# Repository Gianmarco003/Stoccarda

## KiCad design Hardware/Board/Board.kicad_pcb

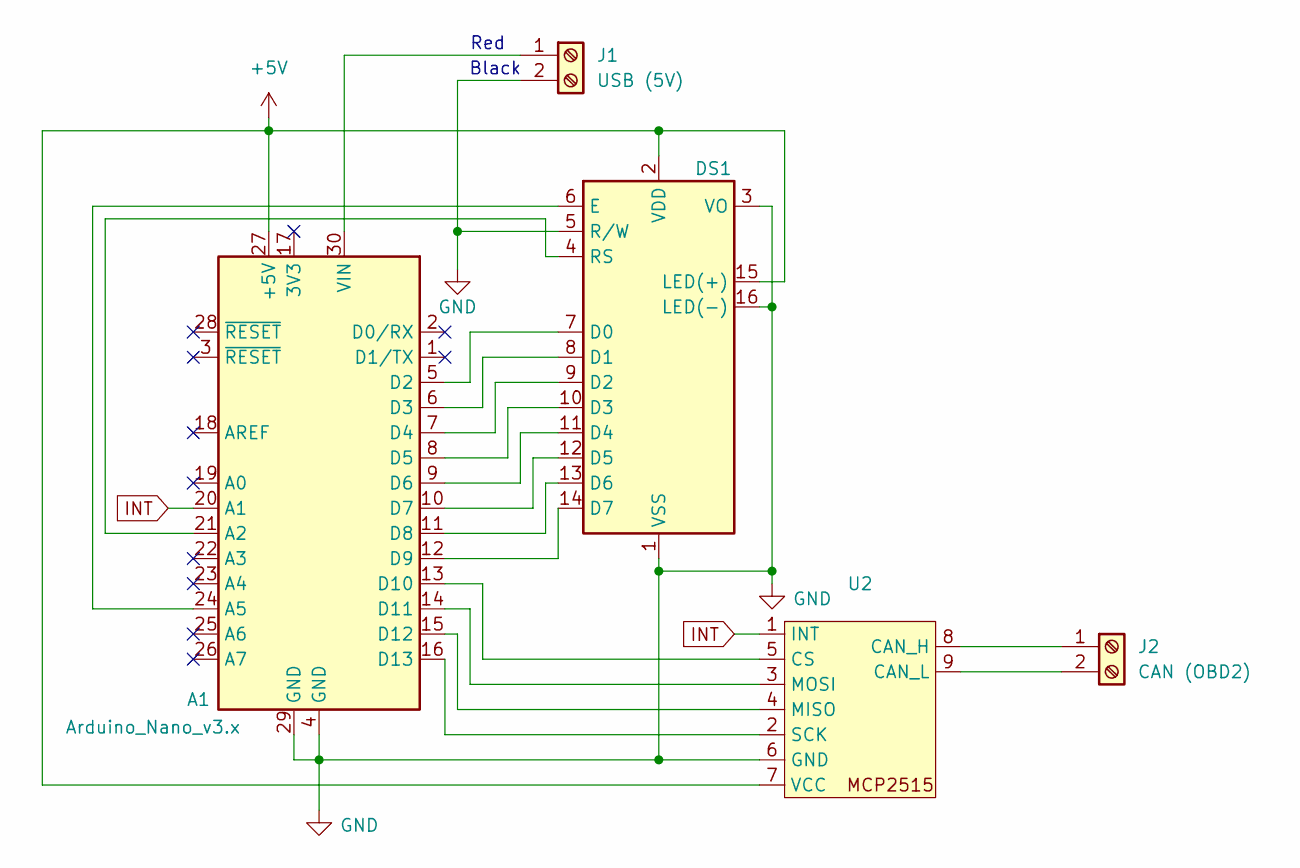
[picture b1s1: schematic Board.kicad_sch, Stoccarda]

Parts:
A1: Arduino_Nano_v3.x; Arduino_Nano
DS1: WC1602A; Display 20x4
J1: USB (5V); PhoenixContact_GMSTBVA_2,5_2-G-7,62_1x02_P7.62mm_Vertical
J2: CAN (OBD2); PhoenixContact_GMSTBVA_2,5_2-G-7,62_1x02_P7.62mm_Vertical
U2: MCP2515 board

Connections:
+5V: A1.27 (+5V), DS1.2 (VDD), DS1.15 (LED(+)), U2.7 (VCC)
GND: A1.4 (GND), A1.29 (GND), DS1.1 (VSS), DS1.3 (VO), DS1.5 (R/W), DS1.16 (LED(-)), J1.2, U2.6 (GND)
INT: A1.20 (A1), U2.1 (INT)
unnamed: A1.21 (A2), DS1.4 (RS)
unnamed: A1.24 (A5), DS1.6 (E)
unnamed: A1.5 (D2), DS1.7 (D0)
unnamed: A1.6 (D3), DS1.8 (D1)
unnamed: A1.7 (D4), DS1.9 (D2)
unnamed: A1.8 (D5), DS1.10 (D3)
unnamed: A1.9 (D6), DS1.11 (D4)
unnamed: A1.10 (D7), DS1.12 (D5)
unnamed: A1.11 (D8), DS1.13 (D6)
unnamed: A1.12 (D9), DS1.14 (D7)
unnamed: A1.13 (D10), U2.5 (CS)
unnamed: A1.14 (D11), U2.3 (MOSI)
unnamed: A1.15 (D12), U2.4 (MISO)
unnamed: A1.16 (D13), U2.2 (SCK)
unnamed: A1.30 (VIN), J1.1
unnamed: J2.1, U2.8 (CAN_H)
unnamed: J2.2, U2.9 (CAN_L)

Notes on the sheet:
Black
Red

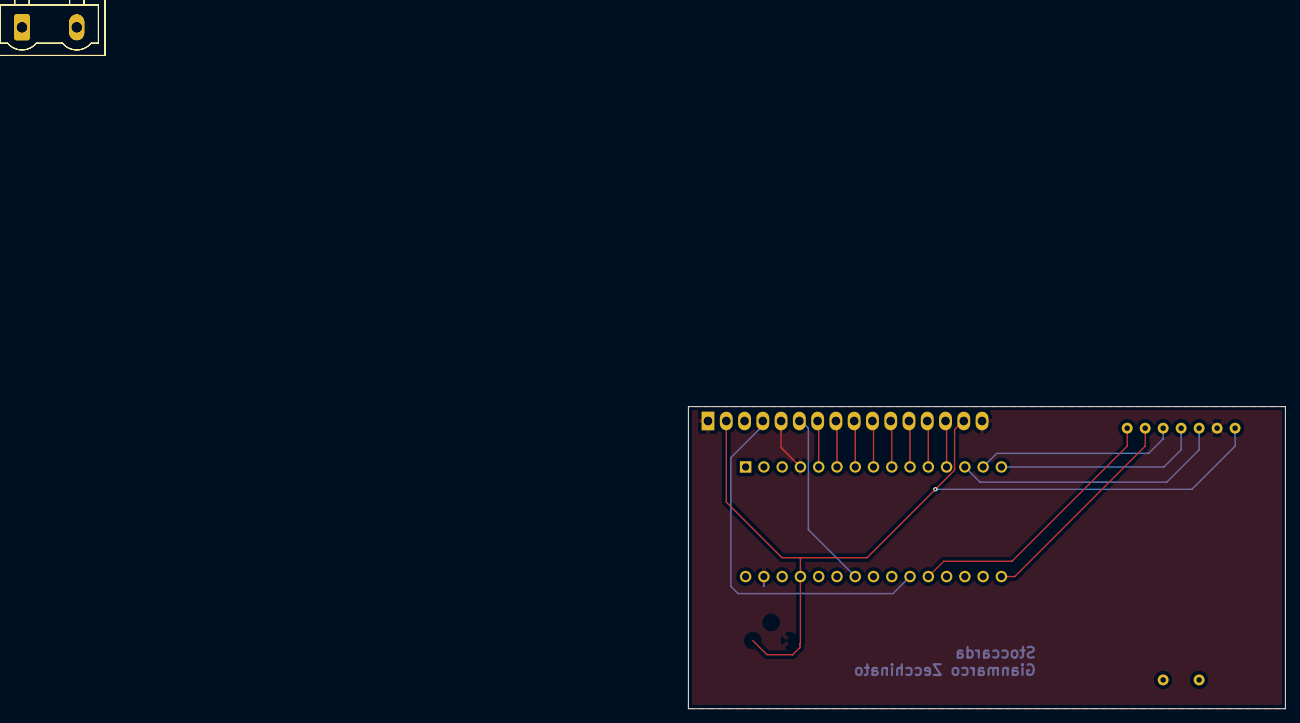
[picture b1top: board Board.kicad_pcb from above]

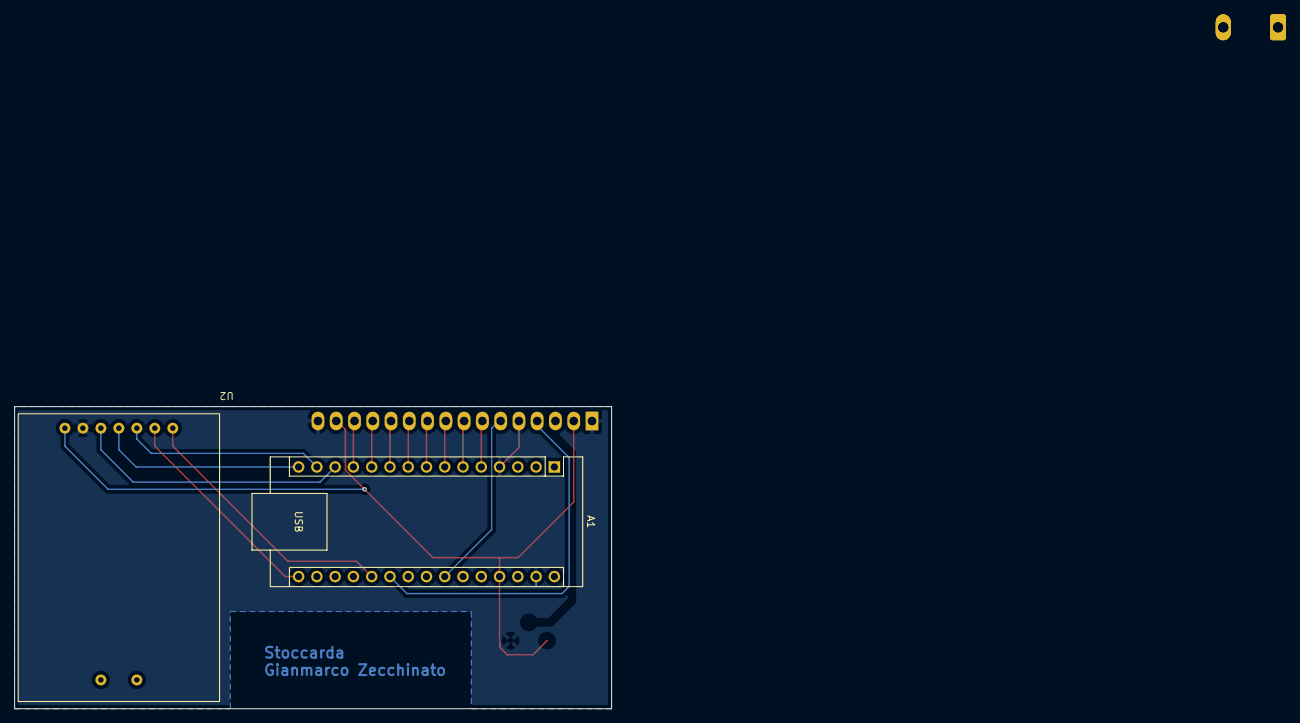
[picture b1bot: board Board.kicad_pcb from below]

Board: 2 copper layers, 83.0 x 42.0 mm, 5 parts (2 on the bottom side), 20 nets.

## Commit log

2025-10-19 Initial commit: Arduino Stoccarda
2025-10-19 Hardware: add KiCad board project
2025-10-19 Add Arduino Nano Pinout.pdf
2025-10-19 Hardware: rename Arduino Nano schematic.pdf
2025-10-20 Firmware: add .gitignore PlatformIO
2025-10-20 Firmware: update acceleration calculation
2025-10-20 Firmware: correct misspelled variable name
2025-11-03 Firmware: add serialData() function for sensor data serial plotting
2025-11-04 Firmware: functions optimization and debug
    Update: accelerationCalc()
    Add: all OBD sensor read at power on
    Update: CatalystTemp1 read start after the first engine start
    Add: delay 100ms in the main loop
2025-11-04 Firmware: acceleration monitor replaced by battery voltage monitoring
2025-11-04 Firmware: update screen formatting
